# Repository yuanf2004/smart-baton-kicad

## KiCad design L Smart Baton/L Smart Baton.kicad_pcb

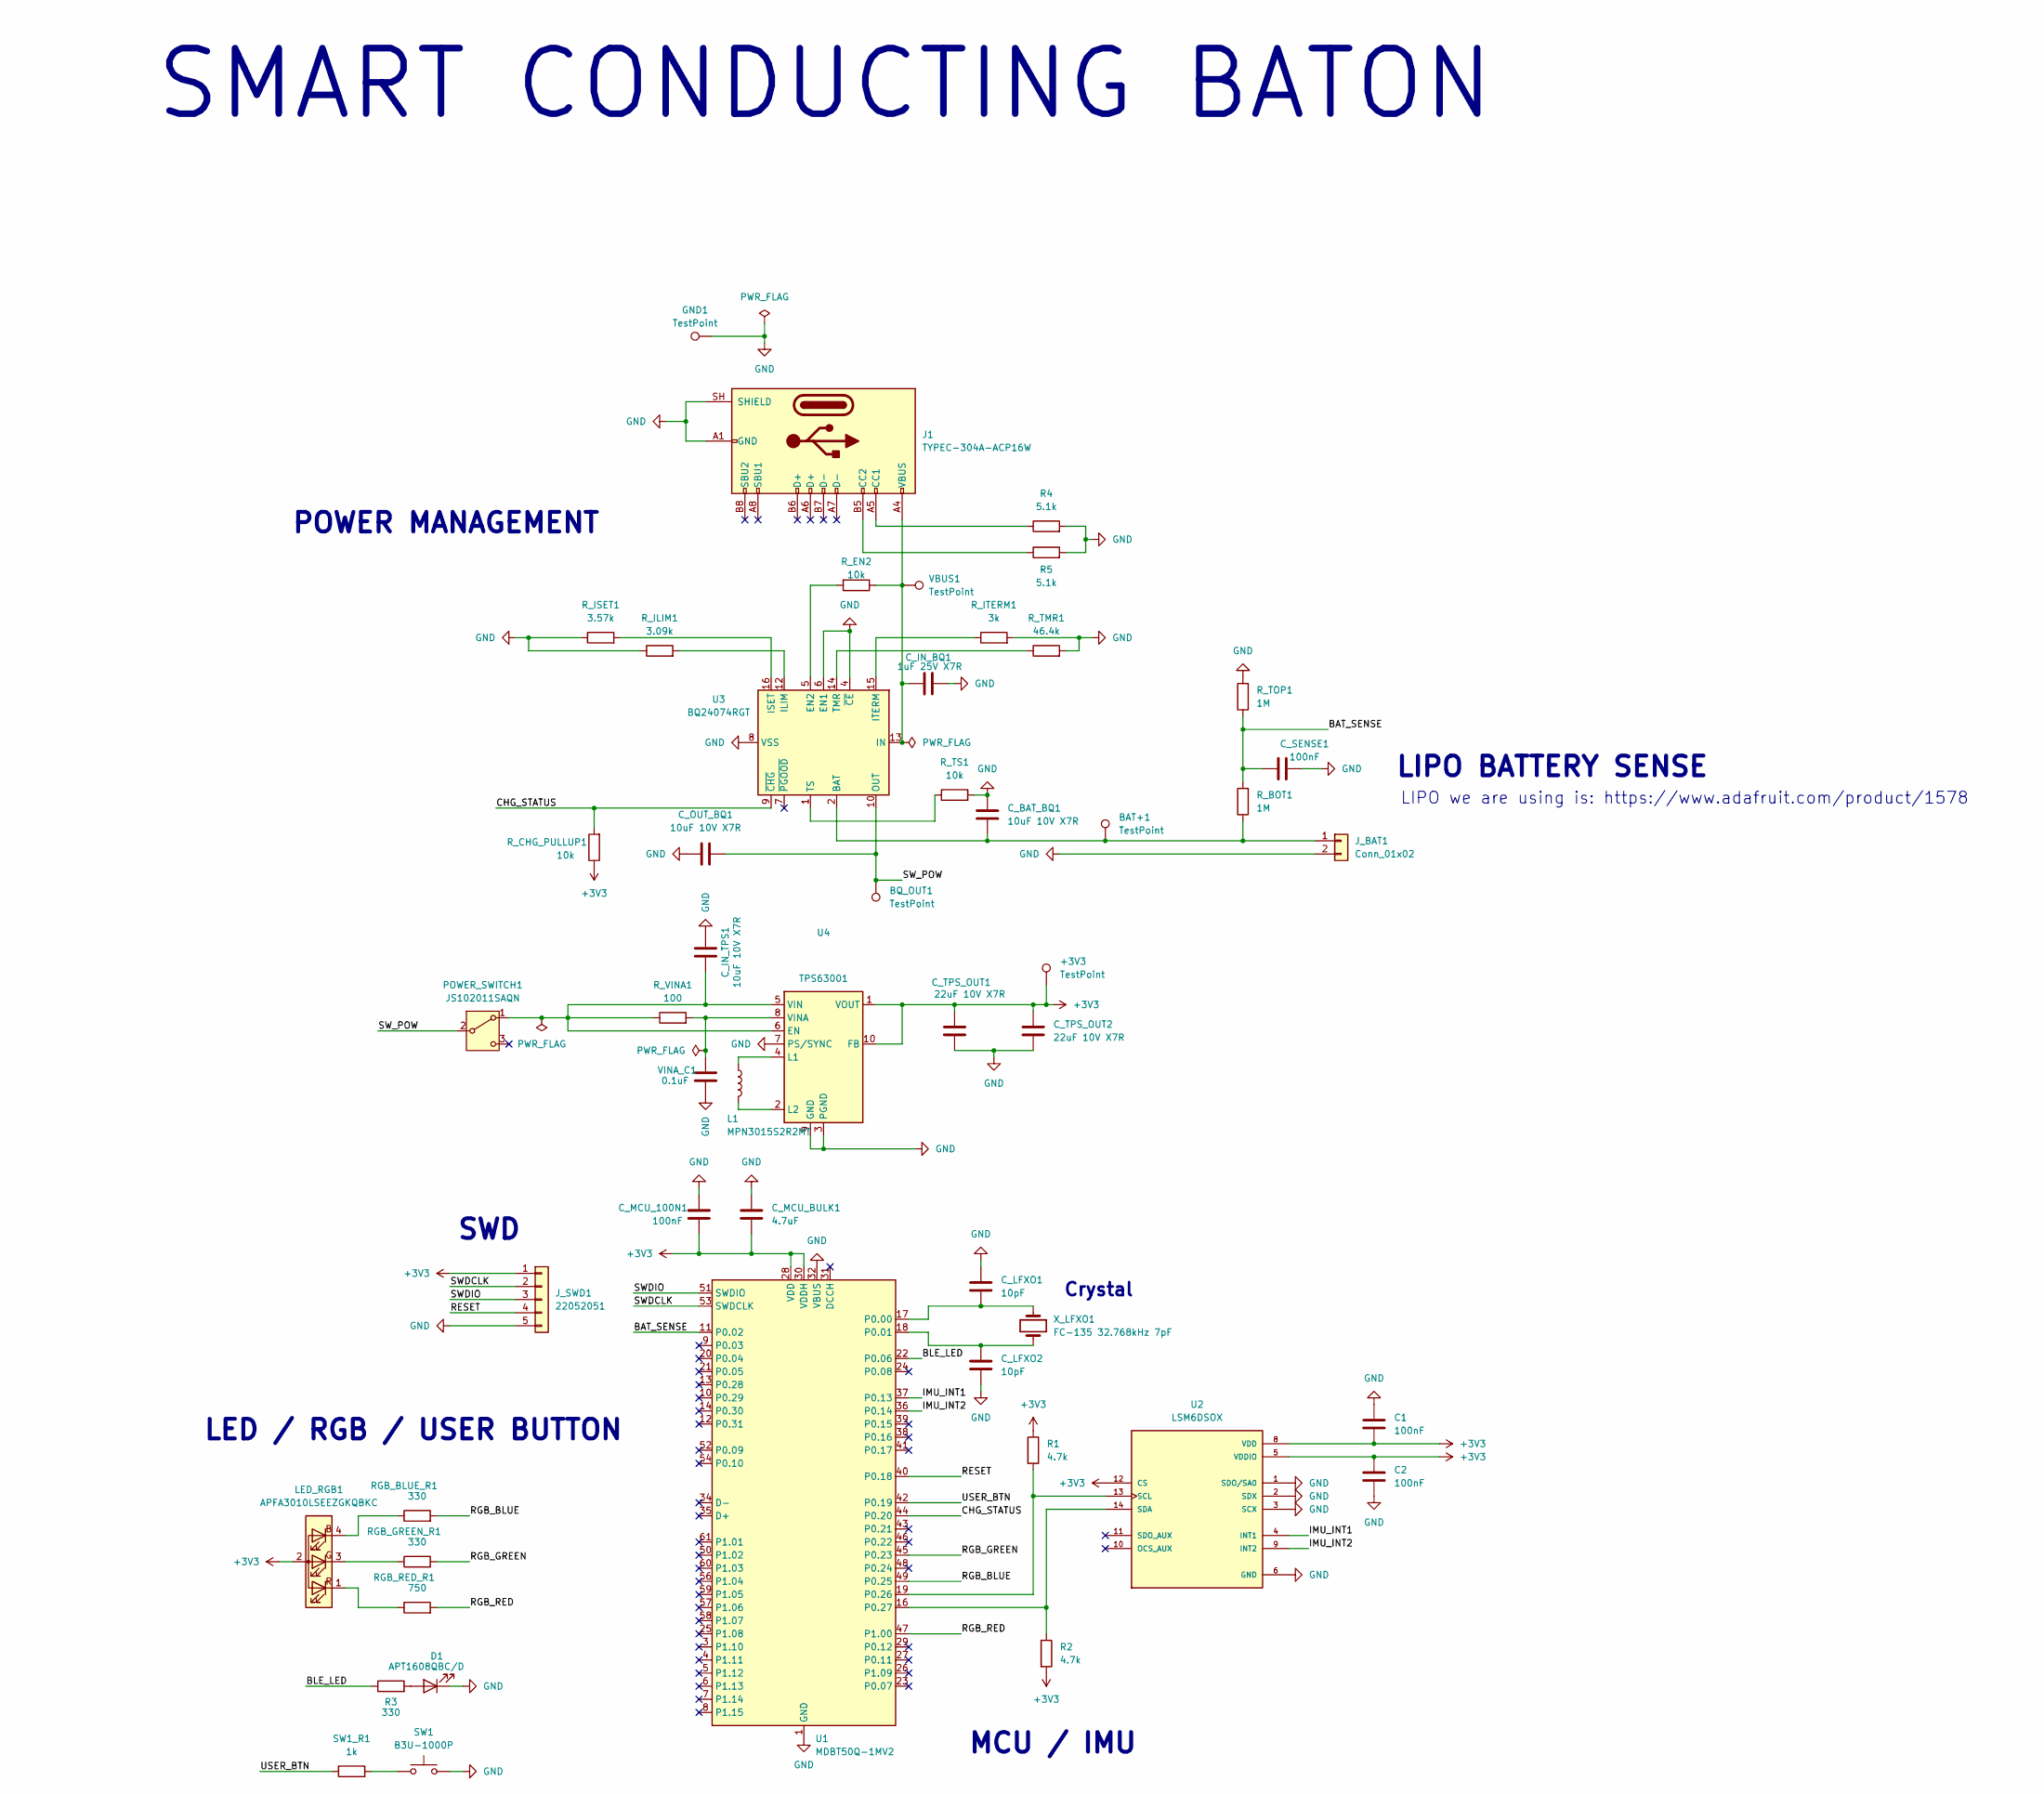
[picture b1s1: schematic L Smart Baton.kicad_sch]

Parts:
+3V3: TestPoint; TestPoint_Pad_D1.0mm
BAT+1: TestPoint; TestPoint_Pad_D1.0mm
BQ_OUT1: TestPoint; TestPoint_Pad_D1.0mm
C1, C2: 100nF; C_0603_1608Metric
C_BAT_BQ1: 10uF 10V X7R; C_0805_2012Metric
C_IN_BQ1: 1uF 25V X7R; C_0805_2012Metric
C_IN_TPS1: 10uF 10V X7R; C_0805_2012Metric
C_LFXO1, C_LFXO2: 10pF; C_0603_1608Metric
C_MCU_100N1: 100nF; C_0603_1608Metric
C_MCU_BULK1: 4.7uF; C_0805_2012Metric
C_OUT_BQ1: 10uF 10V X7R; C_0805_2012Metric
C_SENSE1: 100nF; C_0603_1608Metric
C_TPS_OUT1, C_TPS_OUT2: 22uF 10V X7R; C_0805_2012Metric
D1: APT1608QBC/D; LED_0603_1608Metric
GND1: TestPoint; TestPoint_Pad_D1.0mm
J1: TYPEC-304A-ACP16W; USB_C_Receptacle_GCT_USB4105-xx-A_16P_TopMnt_Horizontal
J_BAT1: Conn_01x02; JST_PH_B2B-PH-K_1x02_P2.00mm_Vertical
J_SWD1: 22052051; PinHeader_1x05_P2.54mm_Horizontal
L1: MPN3015S2R2MT; L_Sunlord_SWPA3015S
LED_RGB1: APFA3010LSEEZGKQBKC; LED_Kingbright_APFA3010_3x1.5mm_Horizontal
POWER_SWITCH1: JS102011SAQN; SW_SPDT_CK_JS102011SAQN
R1, R2: 4.7k; R_0603_1608Metric
R3: 330; R_0603_1608Metric
R4, R5: 5.1k; R_0603_1608Metric
RGB_BLUE_R1: 330; R_0603_1608Metric
RGB_GREEN_R1: 330; R_0603_1608Metric
RGB_RED_R1: 750; R_0603_1608Metric
R_BOT1: 1M; R_0603_1608Metric
R_CHG_PULLUP1: 10k; R_0603_1608Metric
R_EN2: 10k; R_0603_1608Metric
R_ILIM1: 3.09k; R_0603_1608Metric
R_ISET1: 3.57k; R_0603_1608Metric
R_ITERM1: 3k; R_0603_1608Metric
R_TMR1: 46.4k; R_0603_1608Metric
R_TOP1: 1M; R_0603_1608Metric
R_TS1: 10k; R_0603_1608Metric
R_VINA1: 100; R_0603_1608Metric
SW1: B3U-1000P; SW_SPST_B3U-1000P
SW1_R1: 1k; R_0603_1608Metric
U1: MDBT50Q-1MV2; Raytac_MDBT50Q
U2: LSM6DSOX; PQFN50P250X300X86-14N; PARTREV 3.0
U3: BQ24074RGT; VQFN-16-1EP_3x3mm_P0.5mm_EP1.6x1.6mm
U4: TPS63001; Texas_DRC0010J_ThermalVias
VBUS1: TestPoint; TestPoint_Pad_D1.0mm
VINA_C1: 0.1uF; C_0603_1608Metric
X_LFXO1: FC-135 32.768kHz 7pF; Crystal_SMD_3215-2Pin_3.2x1.5mm

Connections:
+3V3: +3V3.1 (1_1), C1.2, C2.1, C_MCU_100N1.2, C_MCU_BULK1.2, C_TPS_OUT1.1, C_TPS_OUT2.1, J_SWD1.1, LED_RGB1.2 (A), R1.1, R2.2, R_CHG_PULLUP1.1, U1.28 (VDD), U1.30 (VDDH), U2.5 (VDDIO), U2.8 (VDD), U2.12 (CS), U4.1 (VOUT), U4.10 (FB)
/BAT_SENSE: C_SENSE1.1, R_BOT1.2, R_TOP1.1, U1.11 (P0.02)
/BLE_LED: R3.1, U1.22 (P0.06)
/CHG_STATUS: R_CHG_PULLUP1.2, U1.44 (P0.20), U3.9 (~CHG)
/IMU_INT1: U1.37 (P0.13), U2.4 (INT1)
/IMU_INT2: U1.36 (P0.14), U2.9 (INT2)
/RESET: J_SWD1.4, U1.40 (P0.18)
/RGB_BLUE: RGB_BLUE_R1.2, U1.49 (P0.25)
/RGB_GREEN: RGB_GREEN_R1.2, U1.45 (P0.23)
/RGB_RED: RGB_RED_R1.2, U1.47 (P1.00)
/SWDCLK: J_SWD1.2, U1.53 (SWDCLK)
/SWDIO: J_SWD1.3, U1.51 (SWDIO)
/SW_POW: BQ_OUT1.1 (1_1), C_OUT_BQ1.2, POWER_SWITCH1.2 (B), U3.10 (OUT), U3.11 (OUT)
/USER_BTN: SW1_R1.1, U1.42 (P0.19)
GND: C1.1, C2.2, C_BAT_BQ1.1, C_IN_BQ1.2, C_IN_TPS1.1, C_LFXO1.2, C_LFXO2.1, C_MCU_100N1.1, C_MCU_BULK1.1, C_OUT_BQ1.1, C_SENSE1.2, C_TPS_OUT1.2, C_TPS_OUT2.2, D1.1 (K), GND1.1 (1_1), J1.A1 (GND), J1.A12 (GND), J1.B1 (GND), J1.B12 (GND), J1.SH (SHIELD), J_BAT1.2, J_SWD1.5, R4.2, R5.2, R_ILIM1.1, R_ISET1.1, R_ITERM1.2, R_TMR1.2, R_TOP1.2, R_TS1.2, SW1.2, U1.1 (GND), U1.2 (GND), U1.15 (GND), U1.32 (VBUS), U1.33 (GND), U1.55 (GND), U2.1 (SDO/SA0), U2.2 (SDX), U2.3 (SCX), U2.6 (GND), U2.7 (GND), U3.4 (~CE), U3.6 (EN1), U3.8 (VSS), U3.17 (VSS), U4.3 (PGND), U4.7 (PS/SYNC), U4.9 (GND), U4.11 (PGND), VINA_C1.1
unnamed: D1.2 (A), R3.2
unnamed: J1.A5 (CC1), R4.1
unnamed: J1.B5 (CC2), R5.1
unnamed: BAT+1.1 (1_1), C_BAT_BQ1.2, J_BAT1.1, R_BOT1.1, U3.2 (BAT), U3.3 (BAT)
unnamed: LED_RGB1.4 (B), RGB_BLUE_R1.1
unnamed: LED_RGB1.3 (G), RGB_GREEN_R1.1
unnamed: LED_RGB1.1 (R), RGB_RED_R1.1
unnamed: C_IN_TPS1.2, POWER_SWITCH1.1 (A), R_VINA1.1, U4.5 (VIN), U4.6 (EN)
unnamed: SW1.1, SW1_R1.2
unnamed: C_LFXO1.1, U1.17 (P0.00), X_LFXO1.1
unnamed: C_LFXO2.2, U1.18 (P0.01), X_LFXO1.2
unnamed: R1.2, U1.19 (P0.26), U2.13 (SCL)
unnamed: R2.1, U1.16 (P0.27), U2.14 (SDA)
unnamed: R_EN2.2, U3.5 (EN2)
unnamed: R_ILIM1.2, U3.12 (ILIM)
unnamed: C_IN_BQ1.1, J1.A4 (VBUS), J1.A9 (VBUS), J1.B4 (VBUS), J1.B9 (VBUS), R_EN2.1, U3.13 (IN), VBUS1.1 (1_1)
unnamed: R_ISET1.2, U3.16 (ISET)
unnamed: R_ITERM1.1, U3.15 (ITERM)
unnamed: R_TMR1.1, U3.14 (TMR)
unnamed: R_TS1.1, U3.1 (TS)
unnamed: L1.1, U4.4 (L1)
unnamed: L1.2, U4.2 (L2)
unnamed: R_VINA1.2, U4.8 (VINA), VINA_C1.2

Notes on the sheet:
SMART CONDUCTING BATON
LED / RGB / USER BUTTON
MCU / IMU
POWER MANAGEMENT
Crystal
LIPO BATTERY SENSE
SWD
LIPO we are using is: https://www.adafruit.com/product/1578

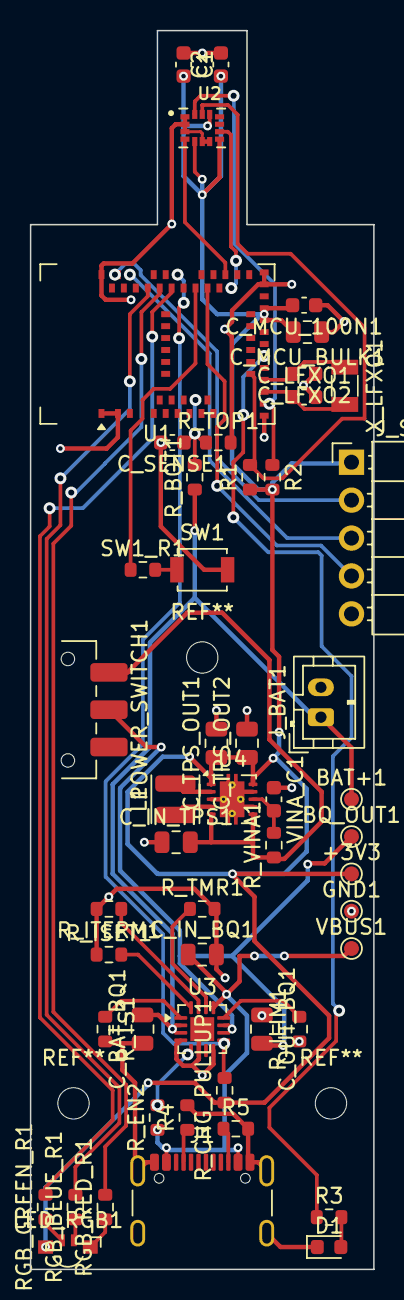
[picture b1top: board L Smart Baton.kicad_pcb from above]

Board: 2 copper layers, 23.0 x 83.0 mm, 51 parts (0 on the bottom side), 38 nets.
